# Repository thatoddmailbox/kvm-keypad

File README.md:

# kvm-keypad

The keypad for the [open-source HDMI KVM switch I built](https://github.com/thatoddmailbox/kvm#kvm). It's a 3x3 array of buttons, allowing you to decide where monitor 1, monitor 2, and the USB devices are routed to.

It connects via a PS/2 cable to [kvm-base](https://github.com/thatoddmailbox/kvm-base#kvm-base)&mdash;however, it does _not_ use the actual PS/2 protocol.

## Useful links
* [Rev A schematic](./mfg/revA/kvm-keypad.pdf)
* [Rev A BOM](./mfg/revA/kvm-keypad.csv)

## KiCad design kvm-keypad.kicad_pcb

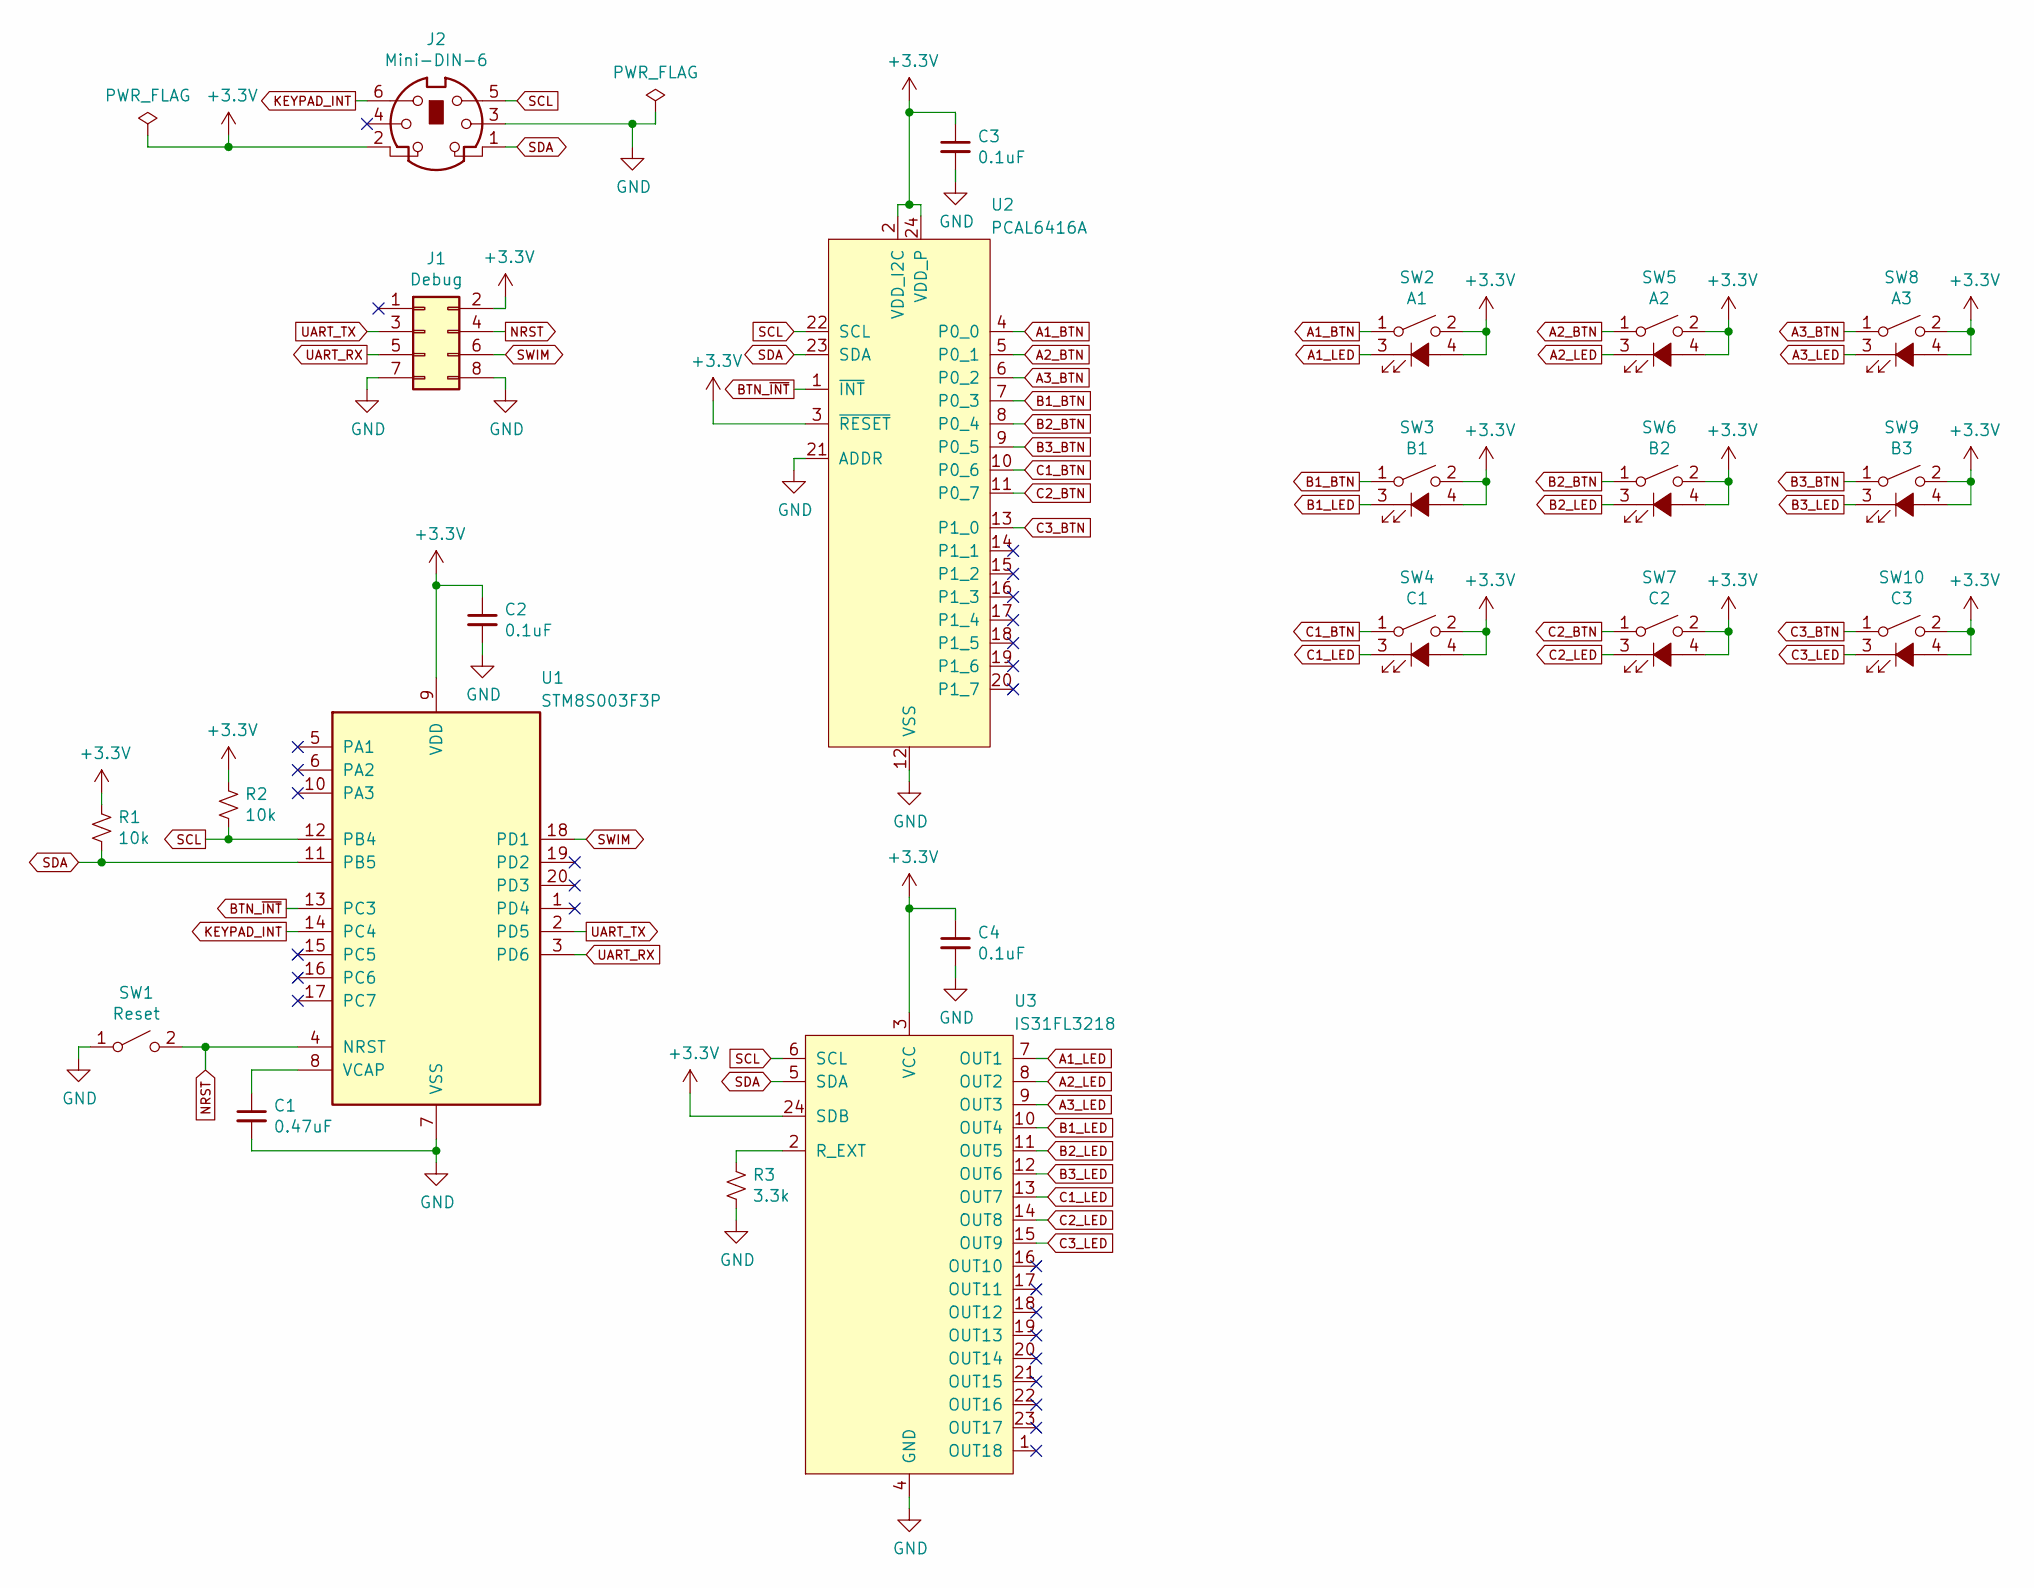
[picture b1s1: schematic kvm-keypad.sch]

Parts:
C1: 0.47uF; C_0603_1608Metric_Pad1.05x0.95mm_HandSolder
C2, C3, C4: 0.1uF; C_0603_1608Metric_Pad1.05x0.95mm_HandSolder
J1: Debug; PinSocket_2x04_P2.54mm_Vertical
J2: Mini-DIN-6; PS2
R1, R2: 10k; R_0603_1608Metric_Pad1.05x0.95mm_HandSolder
R3: 3.3k; R_0603_1608Metric_Pad1.05x0.95mm_HandSolder
SW1: Reset; SW_Push_1P1T_NO_6x6mm_H9.5mm
SW2: A1; K6-1212A
SW3: B1; K6-1212A
SW4: C1; K6-1212A
SW5: A2; K6-1212A
SW6: B2; K6-1212A
SW7: C2; K6-1212A
SW8: A3; K6-1212A
SW9: B3; K6-1212A
SW10: C3; K6-1212A
U1: STM8S003F3P; TSSOP-20_4.4x6.5mm_P0.65mm
U2: PCAL6416A; TSSOP-24_4.4x7.8mm_P0.65mm
U3: IS31FL3218; SOIC-24W_7.5x15.4mm_P1.27mm

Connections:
+3V3: C2.1, C3.1, C4.1, J1.2, J2.2, R1.1, R2.1, SW2.2, SW2.4 (A), SW3.2, SW3.4 (A), SW4.2, SW4.4 (A), SW5.2, SW5.4 (A), SW6.2, SW6.4 (A), SW7.2, SW7.4 (A), SW8.2, SW8.4 (A), SW9.2, SW9.4 (A), SW10.2, SW10.4 (A), U1.9 (VDD), U2.2 (VDD_I2C), U2.3 (~RESET), U2.24 (VDD_P), U3.3 (VCC), U3.24 (SDB)
A1_BTN: SW2.1, U2.4 (P0_0)
A1_LED: SW2.3 (K), U3.7 (OUT1)
A2_BTN: SW5.1, U2.5 (P0_1)
A2_LED: SW5.3 (K), U3.8 (OUT2)
A3_BTN: SW8.1, U2.6 (P0_2)
A3_LED: SW8.3 (K), U3.9 (OUT3)
B1_BTN: SW3.1, U2.7 (P0_3)
B1_LED: SW3.3 (K), U3.10 (OUT4)
B2_BTN: SW6.1, U2.8 (P0_4)
B2_LED: SW6.3 (K), U3.11 (OUT5)
B3_BTN: SW9.1, U2.9 (P0_5)
B3_LED: SW9.3 (K), U3.12 (OUT6)
BTN_~INT: U1.13 (PC3), U2.1 (~INT)
C1_BTN: SW4.1, U2.10 (P0_6)
C1_LED: SW4.3 (K), U3.13 (OUT7)
C2_BTN: SW7.1, U2.11 (P0_7)
C2_LED: SW7.3 (K), U3.14 (OUT8)
C3_BTN: SW10.1, U2.13 (P1_0)
C3_LED: SW10.3 (K), U3.15 (OUT9)
GND: C1.2, C2.2, C3.2, C4.2, J1.7, J1.8, J2.3, R3.2, SW1.1 (A), U1.7 (VSS), U2.12 (VSS), U2.21 (ADDR), U3.4 (GND)
KEYPAD_INT: J2.6, U1.14 (PC4)
NRST: J1.4, SW1.2 (B), U1.4 (NRST)
unnamed: C1.1, U1.8 (VCAP)
unnamed: R3.1, U3.2 (R_EXT)
SCL: J2.5, R2.2, U1.12 (PB4), U2.22 (SCL), U3.6 (SCL)
SDA: J2.1, R1.2, U1.11 (PB5), U2.23 (SDA), U3.5 (SDA)
SWIM: J1.6, U1.18 (PD1)
UART_RX: J1.5, U1.3 (PD6)
UART_TX: J1.3, U1.2 (PD5)

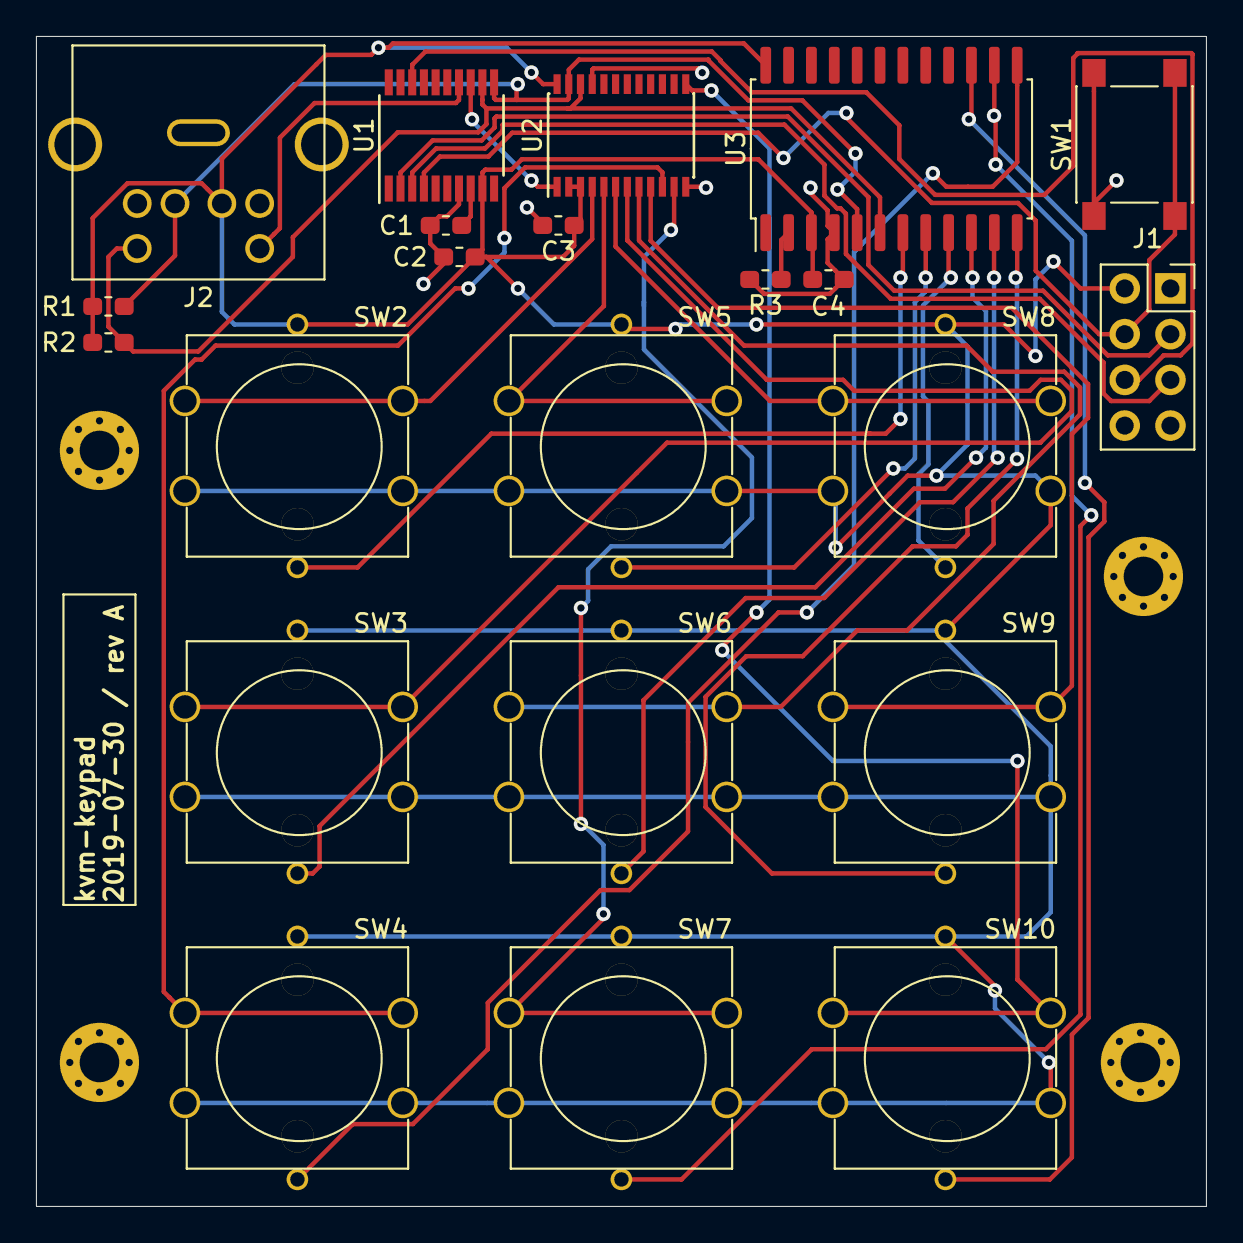
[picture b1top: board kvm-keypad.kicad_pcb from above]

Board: 2 copper layers, 65.0 x 65.0 mm, 22 parts (0 on the bottom side), 30 nets.

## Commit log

2019-07-30 commit rev A schematic, pcb, and gerbers
2021-02-04 add README
2021-02-04 readme: add description
2021-02-04 readme: add note about ps/2 cable
2021-02-04 readme: add link to base repo
2021-02-04 readme: mention that it supports three computers
2021-02-04 readme: clarify that the ps/2 protocl is not useD
2021-02-04 add csv bom file for rev A
2021-02-04 readme: add links to schematic and bom
2021-02-22 add LICENSE
2021-03-24 readme: tweak first line
2021-03-24 readme: link to main kvm repo
2021-03-24 readme: make first line link consistent
2021-03-24 readme: small edits to description
2021-03-24 readme: edit link to kvm-base
2021-04-14 readme: add image
